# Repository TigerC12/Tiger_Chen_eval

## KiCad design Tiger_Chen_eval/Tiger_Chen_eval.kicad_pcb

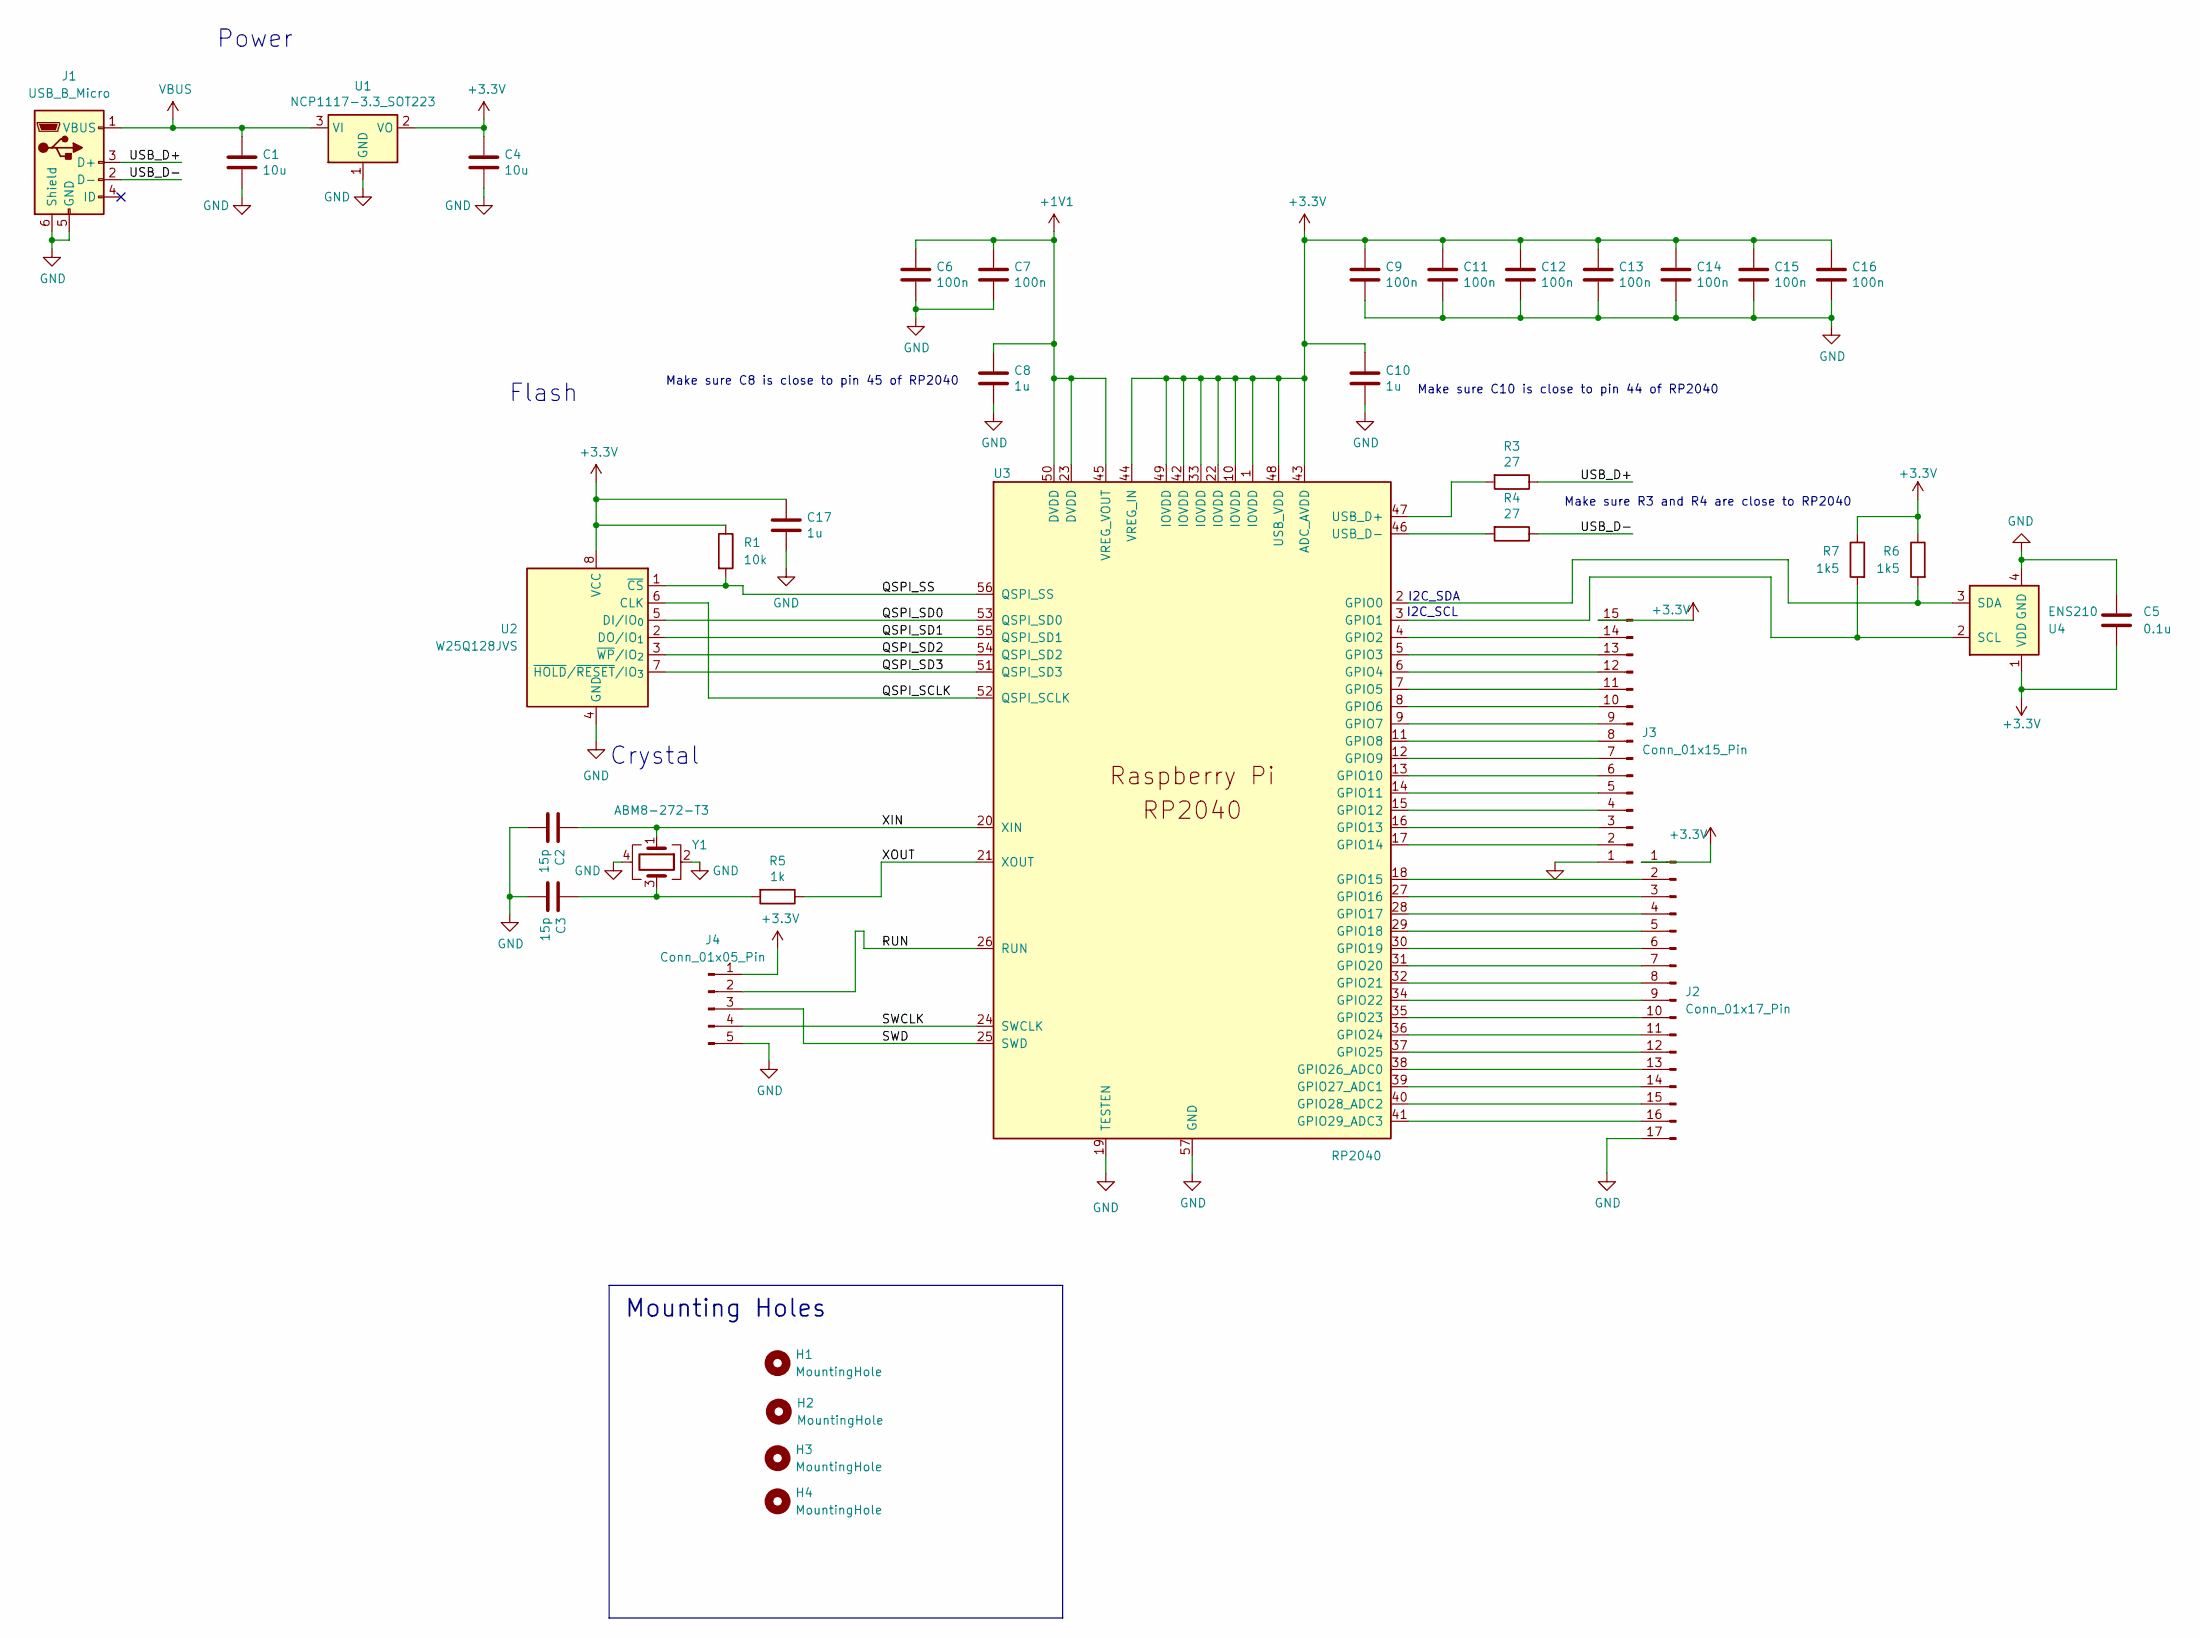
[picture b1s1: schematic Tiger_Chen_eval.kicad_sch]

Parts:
C1, C4: 10u; C_0805_2012Metric
C2, C3: 15p; C_0402_1005Metric
C5: 0.1u; C_0402_1005Metric
C6, C7, C9, C11, C12, C13, C14, C15, C16: 100n; C_0402_1005Metric
C8, C10, C17: 1u; C_0402_1005Metric
H1, H2, H3, H4: MountingHole; MountingHole_2.2mm_M2
J1: USB_B_Micro; USB_Micro-B_Wuerth_629105150521
J2: Conn_01x17_Pin; PinHeader_1x17_P2.54mm_Vertical
J3: Conn_01x15_Pin; PinHeader_1x15_P2.54mm_Vertical
J4: Conn_01x05_Pin; PinHeader_1x05_P2.54mm_Vertical
R1: 10k; R_0402_1005Metric
R3, R4: 27; R_0402_1005Metric
R5: 1k; R_0402_1005Metric
R6, R7: 1k5; R_0402_1005Metric
U1: NCP1117-3.3_SOT223; SOT-223-3_TabPin2
U2: W25Q128JVS; SOIC-8_5.3x5.3mm_P1.27mm
U3: RP2040; QFN-56-1EP_7x7mm_P0.4mm_EP3.2x3.2mm
U4: ENS210; AMS_QFN-4-1EP_2x2mm_P0.95mm_EP0.7x1.6mm
Y1: ABM8-272-T3; Crystal_SMD_3225-4Pin_3.2x2.5mm

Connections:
+1V1: C6.1, C7.1, C8.1, U3.23 (DVDD), U3.45 (VREG_VOUT), U3.50 (DVDD)
+3.3V: C4.1, C5.2, C9.1, C10.1, C11.1, C12.1, C13.1, C14.1, C15.1, C16.1, C17.1, J2.1, J3.15, J4.1, R1.1, R6.1, R7.1, U1.2 (VO), U2.8 (VCC), U3.1 (IOVDD), U3.10 (IOVDD), U3.22 (IOVDD), U3.33 (IOVDD), U3.42 (IOVDD), U3.43 (ADC_AVDD), U3.44 (VREG_IN), U3.48 (USB_VDD), U3.49 (IOVDD), U4.1 (VDD)
/QSPI_SCLK: U2.6 (CLK), U3.52 (QSPI_SCLK)
/QSPI_SD0: U2.5 (DI/IO_{0}), U3.53 (QSPI_SD0)
/QSPI_SD1: U2.2 (DO/IO_{1}), U3.55 (QSPI_SD1)
/QSPI_SD2: U2.3 (~WP/IO_{2}), U3.54 (QSPI_SD2)
/QSPI_SD3: U2.7 (~HOLD/~RESET/IO_{3}), U3.51 (QSPI_SD3)
/QSPI_SS: R1.2, U2.1 (~CS), U3.56 (QSPI_SS)
/RUN: J4.2, U3.26 (RUN)
/SWCLK: J4.4, U3.24 (SWCLK)
/SWD: J4.3, U3.25 (SWD)
/USB_D+: J1.3 (D+), R3.1
/USB_D-: J1.2 (D-), R4.1
/XIN: C2.1, U3.20 (XIN), Y1.1
/XOUT: R5.1, U3.21 (XOUT)
GND: C1.2, C2.2, C3.2, C4.2, C5.1, C6.2, C7.2, C8.2, C9.2, C10.2, C11.2, C12.2, C13.2, C14.2, C15.2, C16.2, C17.2, J1.5 (GND), J1.6 (Shield), J2.17, J3.1, J4.5, U1.1 (GND), U2.4 (GND), U3.19 (TESTEN), U3.57 (GND), U4.4 (GND), U4.5 (GND), Y1.2, Y1.4
unnamed: C3.1, R5.2, Y1.3
unnamed: J2.2, U3.18 (GPIO15)
unnamed: J2.3, U3.27 (GPIO16)
unnamed: J2.4, U3.28 (GPIO17)
unnamed: J2.5, U3.29 (GPIO18)
unnamed: J2.6, U3.30 (GPIO19)
unnamed: J2.7, U3.31 (GPIO20)
unnamed: J2.8, U3.32 (GPIO21)
unnamed: J2.9, U3.34 (GPIO22)
unnamed: J2.10, U3.35 (GPIO23)
unnamed: J2.11, U3.36 (GPIO24)
unnamed: J2.12, U3.37 (GPIO25)
unnamed: J2.13, U3.38 (GPIO26_ADC0)
unnamed: J2.14, U3.39 (GPIO27_ADC1)
unnamed: J2.15, U3.40 (GPIO28_ADC2)
unnamed: J2.16, U3.41 (GPIO29_ADC3)
unnamed: J3.2, U3.17 (GPIO14)
unnamed: J3.3, U3.16 (GPIO13)
unnamed: J3.4, U3.15 (GPIO12)
unnamed: J3.5, U3.14 (GPIO11)
unnamed: J3.6, U3.13 (GPIO10)
unnamed: J3.7, U3.12 (GPIO9)
unnamed: J3.8, U3.11 (GPIO8)
unnamed: J3.9, U3.9 (GPIO7)
unnamed: J3.10, U3.8 (GPIO6)
unnamed: J3.11, U3.7 (GPIO5)
unnamed: J3.12, U3.6 (GPIO4)
unnamed: J3.13, U3.5 (GPIO3)
unnamed: J3.14, U3.4 (GPIO2)
unnamed: R6.2, U3.2 (GPIO0), U4.3 (SDA)
unnamed: R7.2, U3.3 (GPIO1), U4.2 (SCL)
unnamed: R3.2, U3.47 (USB_D+)
unnamed: R4.2, U3.46 (USB_D-)
VBUS: C1.1, J1.1 (VBUS), U1.3 (VI)

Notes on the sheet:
Make sure R3 and R4 are close to RP2040
Crystal
I2C_SDA
Flash
Power
Make sure C10 is close to pin 44 of RP2040
I2C_SCL
Mounting Holes
Make sure C8 is close to pin 45 of RP2040

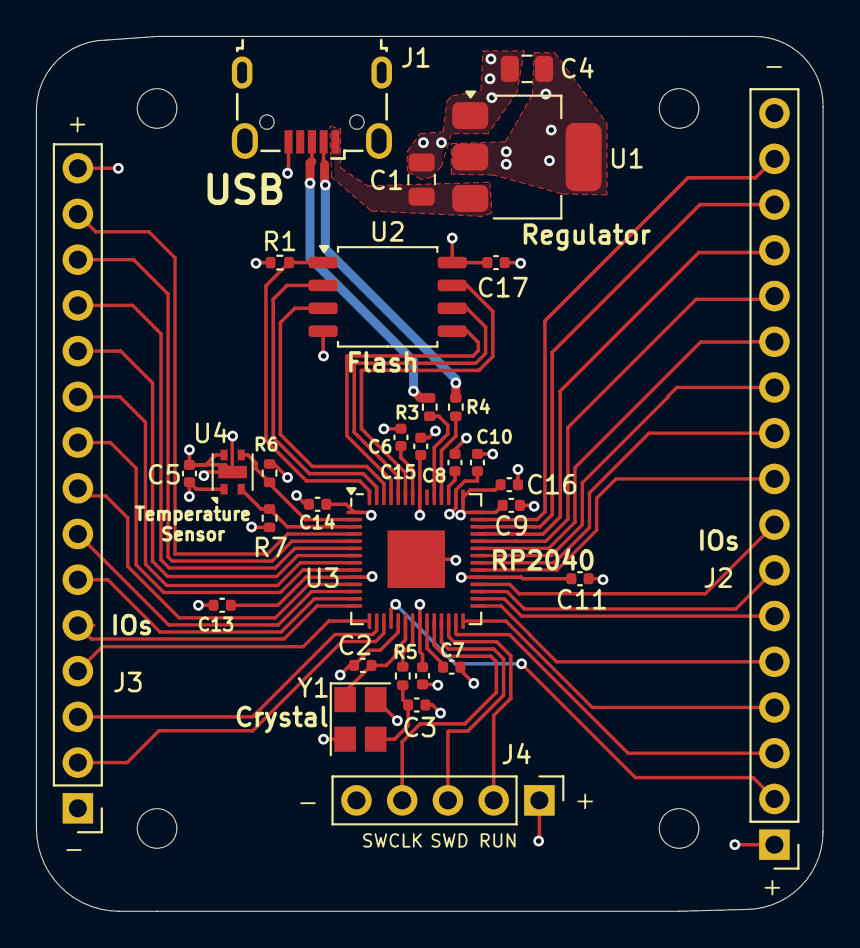
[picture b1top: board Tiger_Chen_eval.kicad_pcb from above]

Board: 4 copper layers, 43.7 x 48.6 mm, 36 parts (0 on the bottom side), 50 nets.

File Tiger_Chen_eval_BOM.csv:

"Reference","Qty","Value","DNP","Exclude from BOM","Exclude from Board","Footprint","Datasheet"
"C1,C4","2","10u","","","","Capacitor_SMD:C_0805_2012Metric","~"
"C2,C3","2","15p","","","","Capacitor_SMD:C_0402_1005Metric","~"
"C5","1","0.1u","","","","Capacitor_SMD:C_0402_1005Metric","~"
"C6,C7,C9,C11,C12,C13,C14,C15,C16","9","100n","","","","Capacitor_SMD:C_0402_1005Metric","~"
"C8,C10,C17","3","1u","","","","Capacitor_SMD:C_0402_1005Metric","~"
"H1,H2,H3,H4","4","MountingHole","","Excluded from BOM","","MountingHole:MountingHole_2.2mm_M2","~"
"J1","1","USB_B_Micro","","","","Connector_USB:USB_Micro-B_Wuerth_629105150521","~"
"J2","1","Conn_01x17_Pin","","","","Connector_PinHeader_2.54mm:PinHeader_1x17_P2.54mm_Vertical","~"
"J3","1","Conn_01x15_Pin","","","","Connector_PinHeader_2.54mm:PinHeader_1x15_P2.54mm_Vertical","~"
"J4","1","Conn_01x05_Pin","","","","Connector_PinHeader_2.54mm:PinHeader_1x05_P2.54mm_Vertical","~"
"R1","1","10k","","","","Resistor_SMD:R_0402_1005Metric","~"
"R3,R4","2","27","","","","Resistor_SMD:R_0402_1005Metric","~"
"R5","1","1k","","","","Resistor_SMD:R_0402_1005Metric","~"
"R6,R7","2","1k5","","","","Resistor_SMD:R_0402_1005Metric","~"
"U1","1","NCP1117-3.3_SOT223","","","","Package_TO_SOT_SMD:SOT-223-3_TabPin2","http://www.onsemi.com/pub_link/Collateral/NCP1117-D.PDF"
"U2","1","W25Q128JVS","","","","Package_SO:SOIC-8_5.3x5.3mm_P1.27mm","https://www.winbond.com/resource-files/w25q128jv_dtr%20revc%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"
"U3","1","RP2040","","","","Package_DFN_QFN:QFN-56-1EP_7x7mm_P0.4mm_EP3.2x3.2mm",""
"U4","1","ENS210","","","","Package_DFN_QFN:AMS_QFN-4-1EP_2x2mm_P0.95mm_EP0.7x1.6mm","http://ams.com/eng/Products/Environmental-Sensors/Relative-H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"
"Y1","1","ABM8-272-T3","","","","Crystal:Crystal_SMD_3225-4Pin_3.2x2.5mm","~"

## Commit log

2025-03-18 added KiCAD project folder
